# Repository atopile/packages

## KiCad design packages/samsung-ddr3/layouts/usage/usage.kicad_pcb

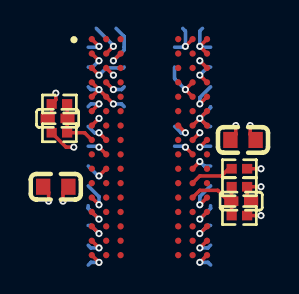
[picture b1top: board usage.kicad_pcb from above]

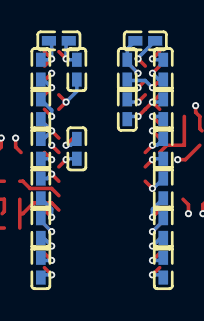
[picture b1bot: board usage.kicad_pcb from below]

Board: 2 copper layers, 28 parts (18 on the bottom side), 6 nets.

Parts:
C1, C2, C5, C6, C7, C8, C9, C10, C11, C12, C13, C14, C15, C16, C17, C18, C19, C20, C21, C22: 100nF ±10% 6.3V X7R; C0402
C3, C4: 10µF ±20% 6.3V X5R; C0603
R1, R2, R3, R4: 1kΩ ±1% 62.5mW; R0402
R5: 240Ω ±1% 62.5mW; R0402
U1: TFBGA-96_L13.0-W7.5-R16-C6-P0.80-TL

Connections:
GND: C1.2, C2.2, C3.2, C4.2, C5.2, C6.2, C7.2, C8.2, C9.2, C10.2, C11.2, C12.2, C13.2, C14.2, C15.2, C16.2, C17.2, C18.2, C19.2, C20.2, C21.2, C22.2, R1.2, R3.2, R5.2, U1.A9, U1.B1, U1.B3, U1.B9, U1.D1, U1.D8, U1.E1, U1.E2, U1.E8, U1.F9, U1.G1, U1.G8, U1.G9, U1.J2, U1.J8, U1.M1, U1.M9, U1.P1, U1.P9, U1.T1, U1.T9
ZQ: R5.1, U1.L8
power-VCC: C3.1, C5.1, C6.1, C7.1, C8.1, C9.1, C10.1, C11.1, C12.1, C13.1, R2.1, R4.1, U1.A1, U1.A8, U1.C1, U1.C9, U1.D2, U1.E9, U1.F1, U1.H2, U1.H9
power_internal-VCC: C4.1, C14.1, C15.1, C16.1, C17.1, C18.1, C19.1, C20.1, C21.1, C22.1, U1.B2, U1.D9, U1.G7, U1.K2, U1.K8, U1.N1, U1.N9, U1.R1, U1.R9
vrefca-VCC: C1.1, R1.1, R2.2, U1.M8
vrefdq-VCC: C2.1, R3.1, R4.2, U1.H1

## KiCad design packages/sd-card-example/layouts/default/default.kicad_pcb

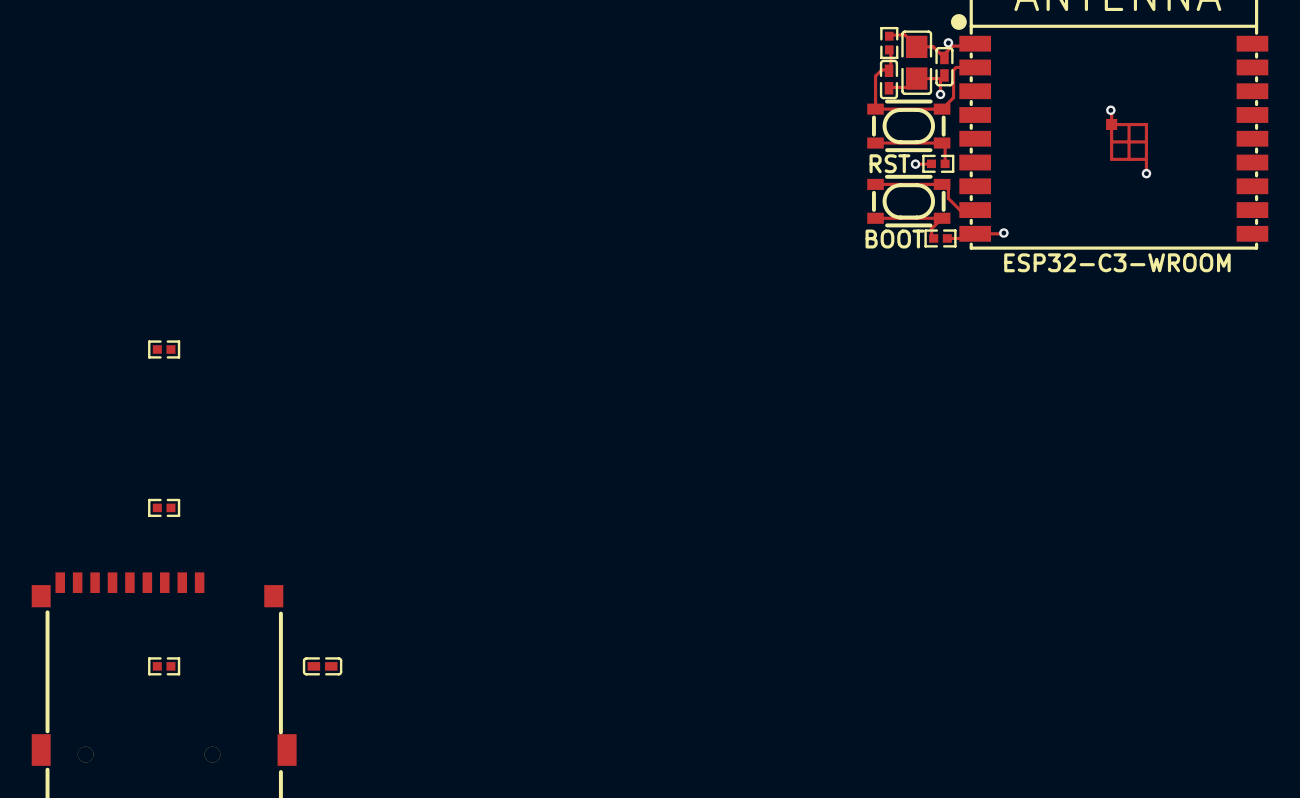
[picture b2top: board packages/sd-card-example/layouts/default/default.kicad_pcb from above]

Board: 2 copper layers, 14 parts (0 on the bottom side), 10 nets.

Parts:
C1, C4: 100nF ±10% 16V X7R; C0402
C2: 10µF ±10% 25V X5R; C0805
C3: 1µF ±10% 25V X5R; C0402
Card1: TF-SMD_TF-01A
R1, R3: 100Ω ±1% 62.5mW; R0402
R2, R4, R5, R6: 10kΩ ±1% 62.5mW; R0402
SW1, SW2: KEY-SMD_4P-L4.2-W3.2-P2.20-LS4.6
U1: BULETM-SMD_ESPRESSIF_ESP32-C3-WROOM-02-N4-4MB

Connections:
CLK: Card1.5, R6.1
GND: Card1.10, Card1.11, Card1.12, Card1.13
gnd: C1.2, C2.2, C3.2, C4.2, Card1.6, R1.2, R3.2, U1.9, U1.19
hv: C1.1, C2.1, C4.1, Card1.4, R2.2, R4.2, R5.2, R6.2, U1.1
input-0: R1.1, SW1.1, SW1.2
input-1: R3.1, SW2.1, SW2.2
output-0: SW1.3, SW1.4, U1.8
output-1: C3.1, R2.1, SW2.3, SW2.4, U1.2
pins[6]: Card1.7, R4.1
pins[7]: Card1.8, R5.1

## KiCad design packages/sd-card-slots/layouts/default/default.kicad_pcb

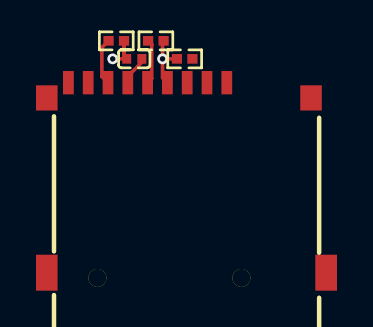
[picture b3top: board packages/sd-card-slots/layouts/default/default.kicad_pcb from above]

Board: 2 copper layers, 5 parts (0 on the bottom side), 6 nets.

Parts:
C1: 100nF; C0402
Card1: TF-SMD_TF-01A
R1, R2, R3: 10kΩ; R0402

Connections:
GND: Card1.10, Card1.11, Card1.12, Card1.13
MISO: Card1.7, R1.1
MOSI: Card1.3, R2.1
SCLK: Card1.5, R3.1
hv: C1.1, Card1.4, R1.2, R2.2, R3.2
lv: C1.2, Card1.6

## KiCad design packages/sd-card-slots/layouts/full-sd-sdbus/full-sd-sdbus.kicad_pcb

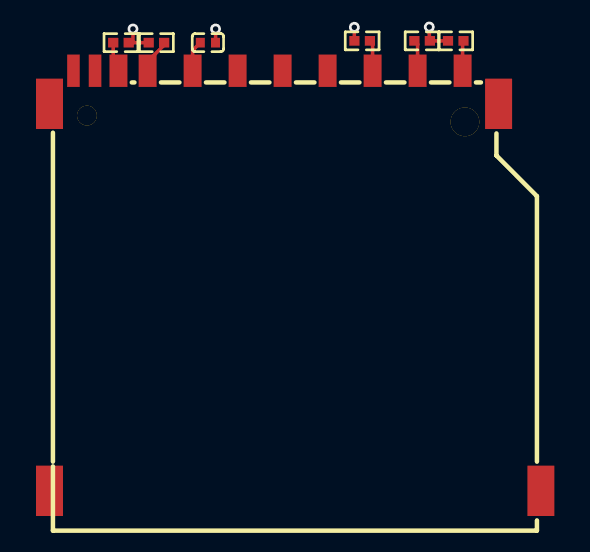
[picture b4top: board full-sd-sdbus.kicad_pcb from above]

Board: 2 copper layers, 7 parts (0 on the bottom side), 7 nets.

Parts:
C1: 100nF; C0402
Card1: SIM-SMD_SD-102
R1, R2, R3, R4, R5: 10kΩ; R0402

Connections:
CMD: Card1.2, R1.1
hv: C1.1, Card1.4, R1.2, R2.2, R3.2, R4.2, R5.2
lv: C1.2, Card1.3, Card1.6, Card1.12, Card1.13, Card1.14, Card1.15
pins[0]: Card1.1, R5.1
pins[6]: Card1.7, R2.1
pins[7]: Card1.8, R3.1
pins[8]: Card1.9, R4.1
